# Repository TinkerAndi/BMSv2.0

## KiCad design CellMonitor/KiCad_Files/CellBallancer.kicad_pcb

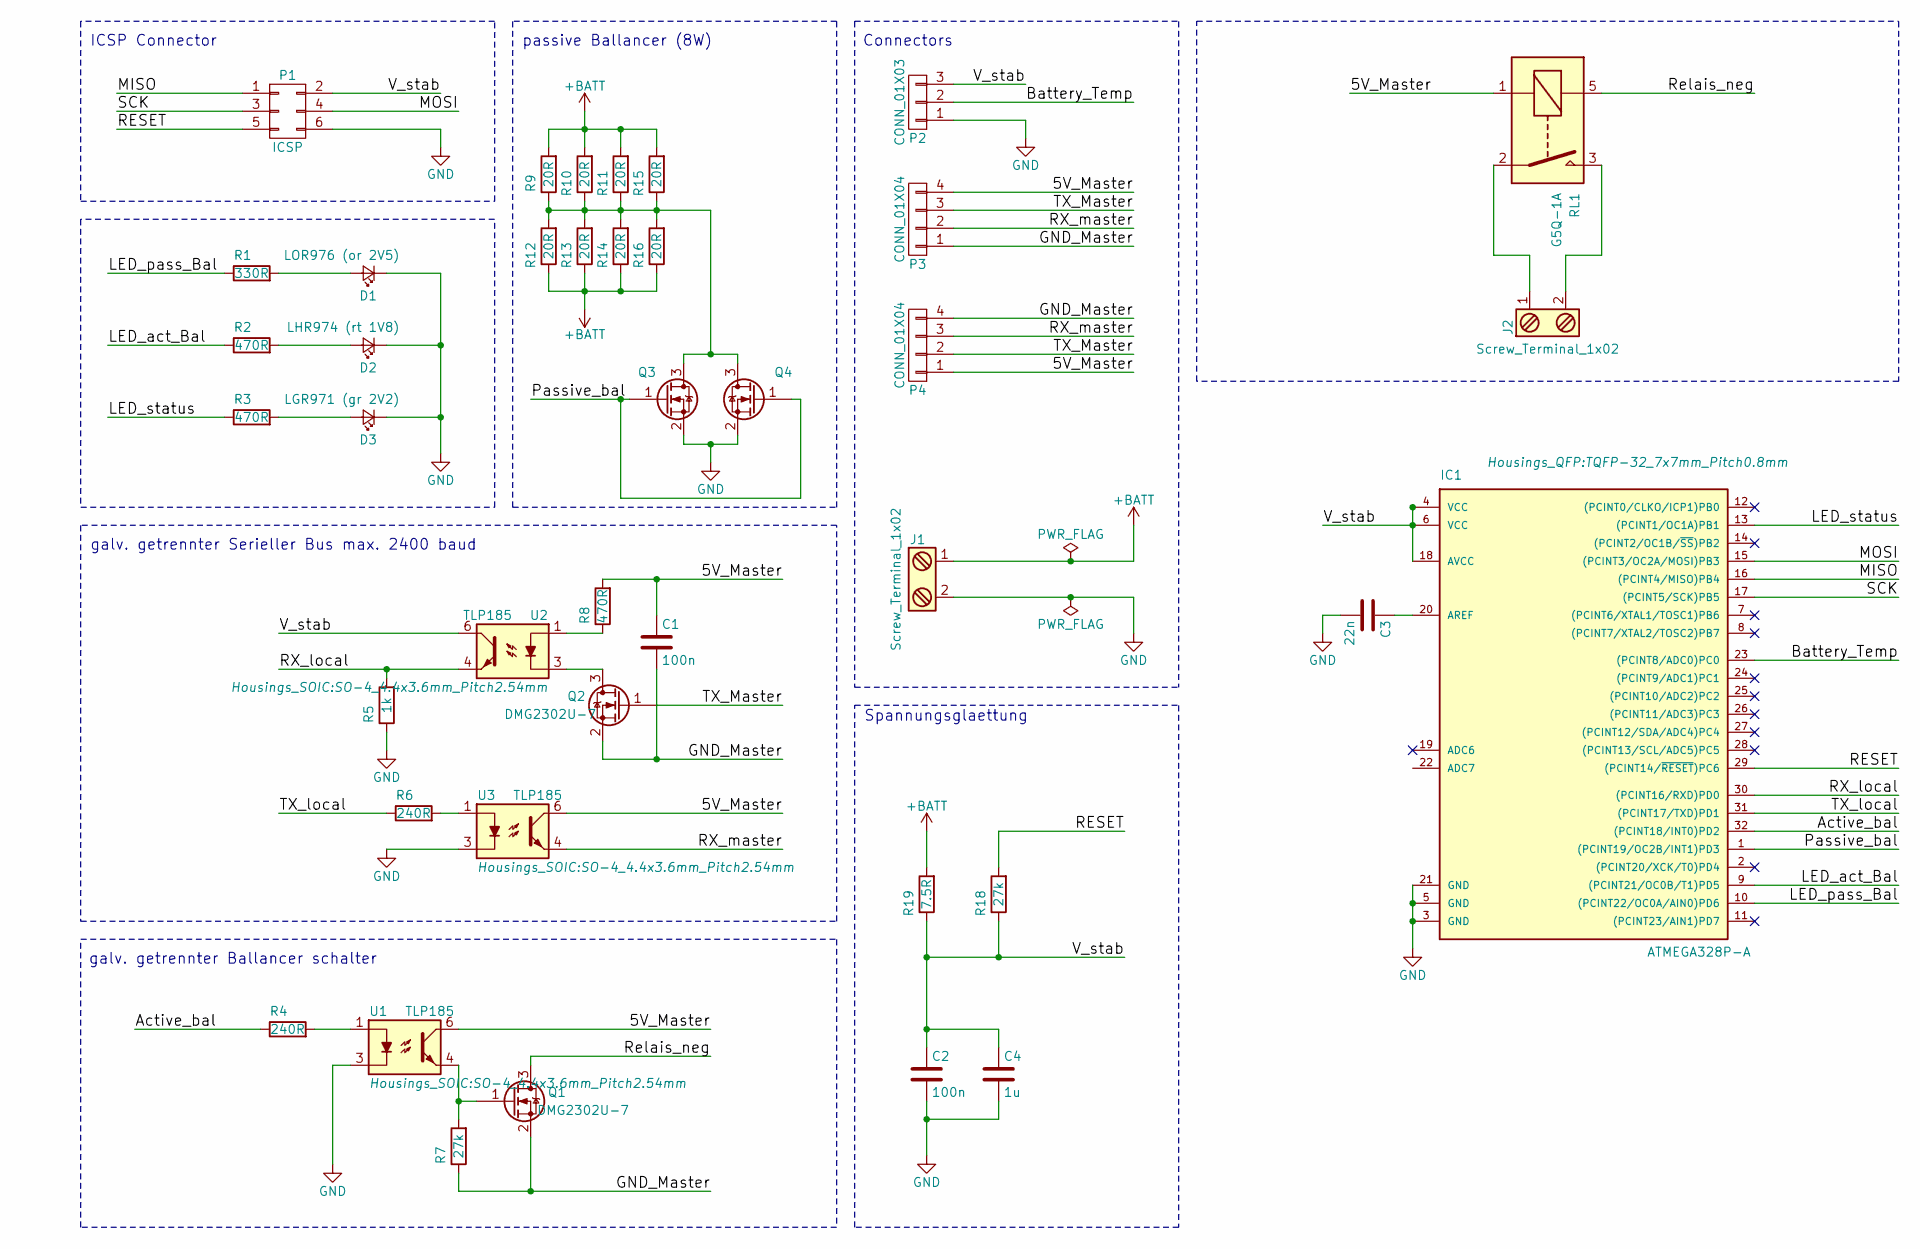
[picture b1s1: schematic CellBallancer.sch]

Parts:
C1, C2: 100n; R_0805_HandSoldering
C3: 22n; R_0805_HandSoldering
C4: 1u; R_0805_HandSoldering
D1: LOR976 (or 2V5); R_0805_HandSoldering
D2: LHR974 (rt 1V8); R_0805_HandSoldering
D3: LGR971 (gr 2V2); R_0805_HandSoldering
IC1: ATMEGA328P-A; TQFP-32_7x7mm_Pitch0.8mm
J1, J2: Screw_Terminal_1x02; bornier2
P1: ICSP; Pin_Header_Straight_2x03_Pitch2.54mm
P2: CONN_01X03; Pin_Header_Angled_1x03_Pitch2.54mm
P3, P4: CONN_01X04; Pin_Header_Angled_1x04_Pitch2.54mm
Q1, Q2, Q3, Q4: DMG2302U-7; SOT-23
R1: 330R; R_0805_HandSoldering
R2, R3, R8: 470R; R_0805_HandSoldering
R4, R6: 240R; R_0805_HandSoldering
R5: 1k; R_0805_HandSoldering
R7, R18: 27k; R_0805_HandSoldering
R9, R10, R11, R12, R13, R14, R15, R16: 20R; R_2512_HandSoldering
R19: 7.5R; R_2512
RL1: G5Q-1A; Relay_SPST_OMRON-G5Q
U1, U2, U3: TLP185; SO-4_4.4x3.6mm_Pitch2.54mm

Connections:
+BATT: J1.1, R9.2, R10.2, R11.2, R12.1, R13.1, R14.1, R15.2, R16.1, R19.2
/5V_Master: C1.1, P3.4, P4.1, R8.2, RL1.1, U1.6, U3.6
/Active_bal: IC1.32 ((PCINT18/INT0)PD2), R4.1
/Battery_Temp: IC1.23 ((PCINT8/ADC0)PC0), P2.2
/GND_Master: C1.2, P3.1, P4.4, Q1.2 (S), Q2.2 (S), R7.1
/LED_act_Bal: IC1.9 ((PCINT21/OC0B/T1)PD5), R2.1
/LED_pass_Bal: IC1.10 ((PCINT22/OC0A/AIN0)PD6), R1.1
/LED_status: IC1.13 ((PCINT1/OC1A)PB1), R3.1
/MISO: IC1.16 ((PCINT4/MISO)PB4), P1.1
/MOSI: IC1.15 ((PCINT3/OC2A/MOSI)PB3), P1.4
/Passive_bal: IC1.1 ((PCINT19/OC2B/INT1)PD3), Q3.1 (G), Q4.1 (G)
/RESET: IC1.29 ((PCINT14/~RESET~)PC6), P1.5, R18.2
/RX_local: IC1.30 ((PCINT16/RXD)PD0), R5.2, U2.4
/RX_master: P3.2, P4.3, U3.4
/Relais_neg: Q1.3 (D), RL1.5
/SCK: IC1.17 ((PCINT5/SCK)PB5), P1.3
/TX_Master: P3.3, P4.2, Q2.1 (G)
/TX_local: IC1.31 ((PCINT17/TXD)PD1), R6.1
/V_stab: C2.1, C4.1, IC1.4 (VCC), IC1.6 (VCC), IC1.18 (AVCC), P1.2, P2.3, R18.1, R19.1, U2.6
GND: C2.2, C3.2, C4.2, D1.1 (K), D2.1 (K), D3.1 (K), IC1.3 (GND), IC1.5 (GND), IC1.21 (GND), J1.2, P1.6, P2.1, Q3.2 (S), Q4.2 (S), R5.1, U1.3, U3.3
unnamed: C3.1, IC1.20 (AREF)
unnamed: D1.2 (A), R1.2
unnamed: D2.2 (A), R2.2
unnamed: D3.2 (A), R3.2
unnamed: J2.1, RL1.2
unnamed: J2.2, RL1.3
unnamed: Q1.1 (G), R7.2, U1.4
unnamed: Q2.3 (D), U2.3
unnamed: Q3.3 (D), Q4.3 (D), R9.1, R10.1, R11.1, R12.2, R13.2, R14.2, R15.1, R16.2
unnamed: R4.2, U1.1
unnamed: R6.2, U3.1
unnamed: R8.1, U2.1

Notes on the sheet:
passive Ballancer (8W)
ICSP Connector
galv. getrennter Serieller Bus max. 2400 baud
galv. getrennter Ballancer schalter
Connectors
Spannungsglaettung

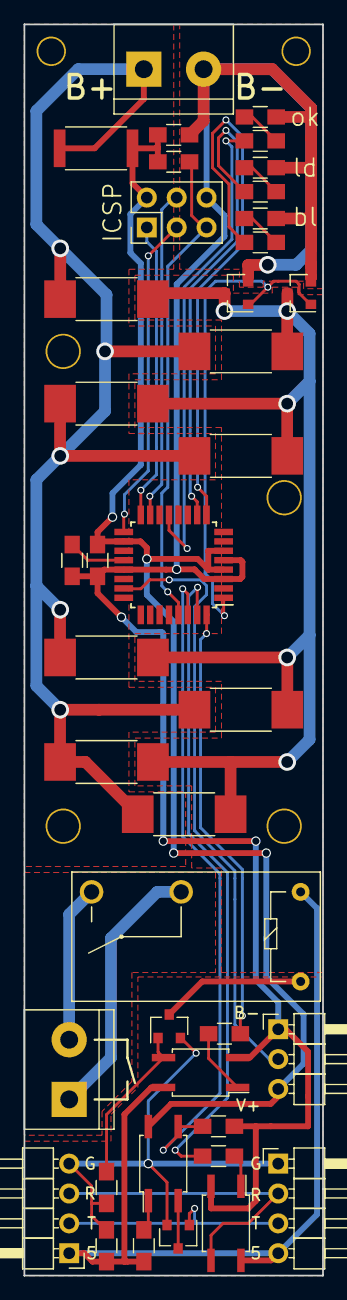
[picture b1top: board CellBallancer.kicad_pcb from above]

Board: 2 copper layers, 25.4 x 106.4 mm, 40 parts (0 on the bottom side), 32 nets.

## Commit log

2017-12-29 initial Commit of Nextion-HMI Files
2017-12-29 Initial Commit of Mater Firmware
2017-12-29 added directories and files to be ignored in AtmelStudio 7 Solutions
2017-12-29 initial Commit of c++ source files depending to Master and slave code
2017-12-29 Initial commit of slave Firmware
2017-12-29 documentation about the hardware used
2017-12-29 Initial Commit of schematic and board layout of Cell-Monitor-Slave
2017-12-29 new excusion of gerber file-folder
2017-12-29 changes only the project file
2018-01-01 add screen for viewing Slavetable and coosing the Cell number
2018-01-01 no idea what Atmel Studio has changed
2018-01-01 LoggMarker double mark bug fixed
2018-01-01 safety commit while develloping slave to master communication its an non working state
2018-01-01 Atmel Studio has done changes to the project file
2018-01-02 working state building proper Master Slave conversion
2018-02-13 bigger mounting holes
2018-02-13 Master Slave adressig works
2018-02-21 Slave Nummerierung ueber Slave_Conf Display und Identificatin blink fertig
2018-02-21 Bugfix rec Data from Display; EEPROM storage of Slave Table; Slave search and edit via Display Menu; Identification blink via display button; whole search new slave rebuild; cyclic communication is n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
2018-02-25 Communication with data send from slave added
2018-03-01 Display Test buttons
2018-03-01 non working commit
